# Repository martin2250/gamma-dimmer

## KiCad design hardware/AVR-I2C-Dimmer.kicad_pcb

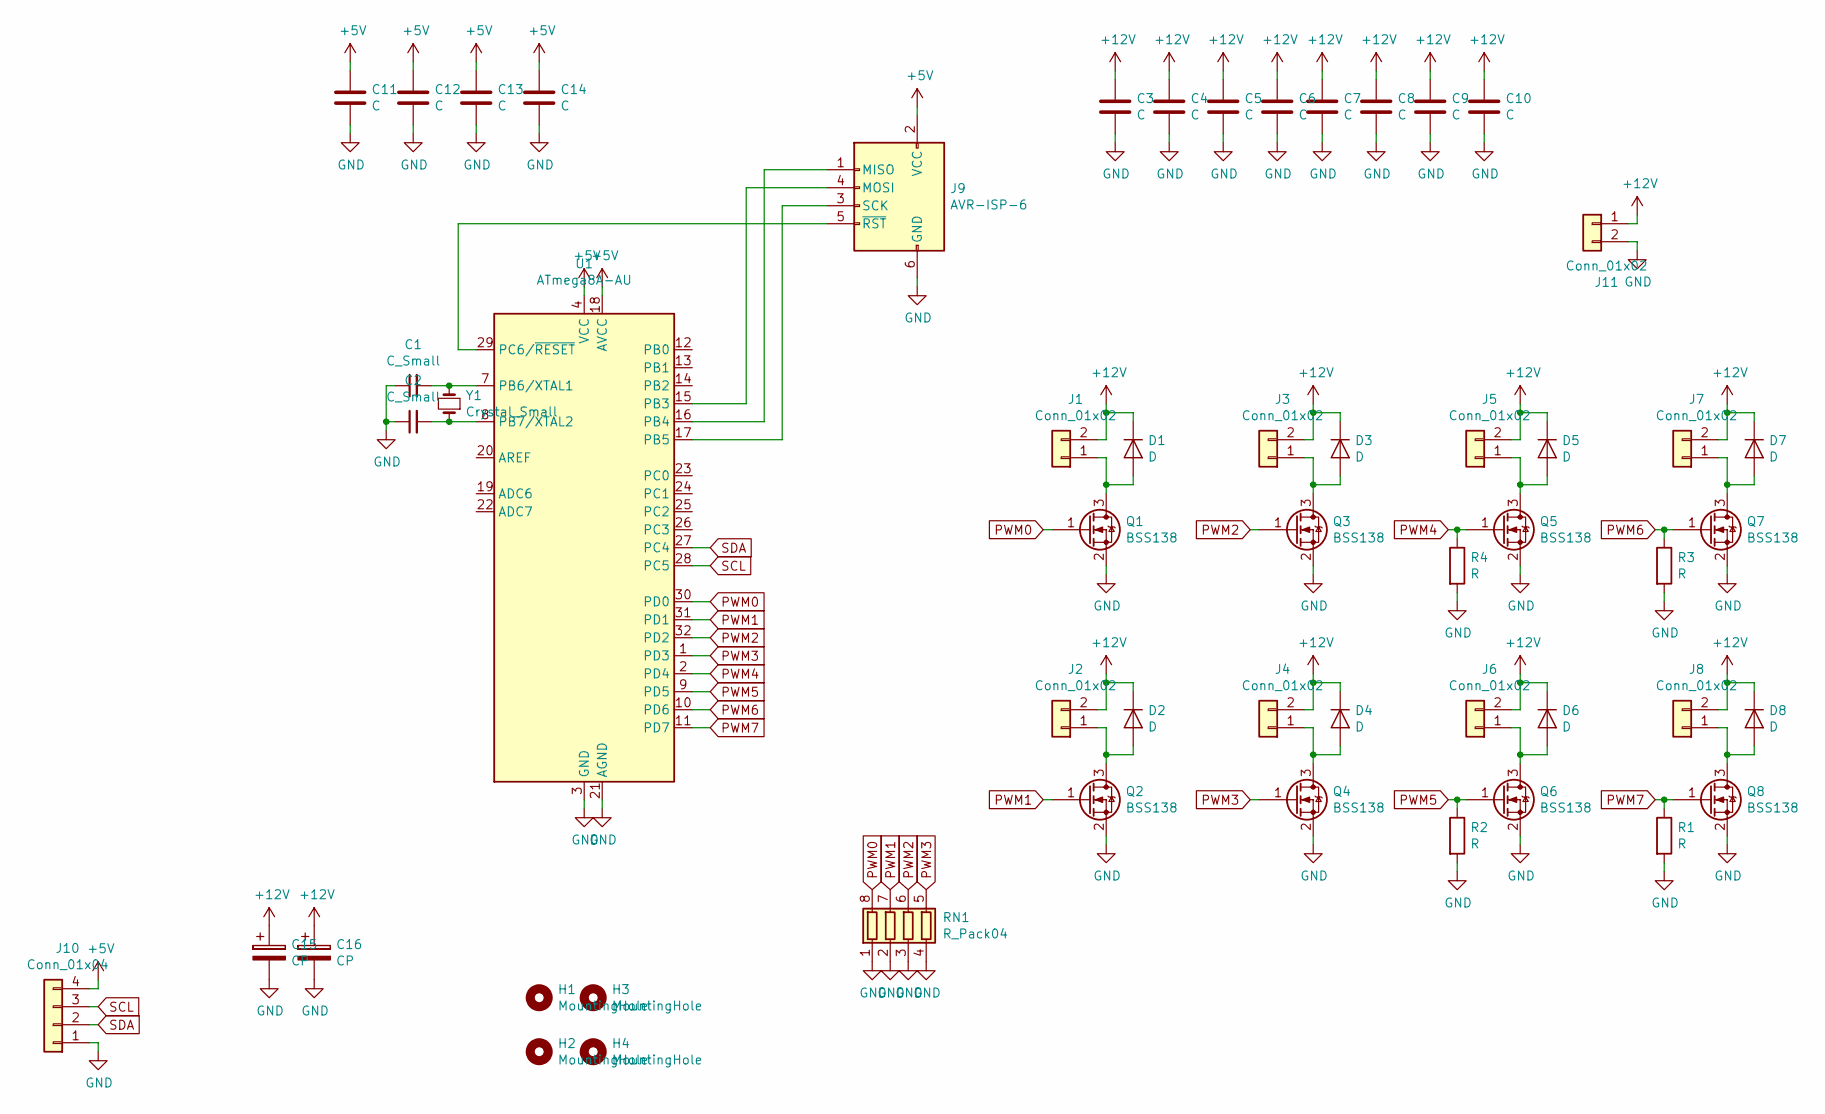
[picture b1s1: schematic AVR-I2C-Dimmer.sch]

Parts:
C1, C2: C_Small; C_0805_2012Metric_Pad1.15x1.40mm_HandSolder
C3, C4, C5, C6, C7, C8, C9, C10: C; C_1206_3216Metric_Pad1.42x1.75mm_HandSolder
C11, C12, C13, C14: C; C_0805_2012Metric_Pad1.15x1.40mm_HandSolder
C15, C16: CP; CP_Radial_D8.0mm_P3.50mm
D1, D2, D3, D4, D5, D6, D7, D8: D; D_MiniMELF
H1, H2, H3, H4: MountingHole; MountingHole_3.2mm_M3
J1, J2, J3, J4, J5, J6, J7, J8, J11: Conn_01x02; TerminalBlock_4Ucon_1x02_P3.50mm_Horizontal
J9: AVR-ISP-6; PinHeader_2x03_P2.54mm_Vertical
J10: Conn_01x04; PinHeader_1x04_P2.54mm_Vertical
Q1, Q2, Q3, Q4, Q5, Q6, Q7, Q8: BSS138; SOT-23
R1, R2, R3, R4: R; R_0805_2012Metric
RN1: R_Pack04; R_Array_Concave_4x0603
U1: ATmega8A-AU; TQFP-32_7x7mm_P0.8mm
Y1: Crystal_Small; Crystal_HC49-U_Vertical

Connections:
+5V: C11.1, C12.1, C13.1, C14.1, J9.2 (VCC), J10.4, U1.4 (VCC), U1.6 (VCC), U1.18 (AVCC)
+12V: C3.1, C4.1, C5.1, C6.1, C7.1, C8.1, C9.1, C10.1, C15.1, C16.1, D1.1 (K), D2.1 (K), D3.1 (K), D4.1 (K), D5.1 (K), D6.1 (K), D7.1 (K), D8.1 (K), J1.2, J2.2, J3.2, J4.2, J5.2, J6.2, J7.2, J8.2, J11.1
GND: C1.1, C2.1, C3.2, C4.2, C5.2, C6.2, C7.2, C8.2, C9.2, C10.2, C11.2, C12.2, C13.2, C14.2, C15.2, C16.2, J9.6 (GND), J10.1, J11.2, Q1.2 (S), Q2.2 (S), Q3.2 (S), Q4.2 (S), Q5.2 (S), Q6.2 (S), Q7.2 (S), Q8.2 (S), R1.2, R2.2, R3.2, R4.2, RN1.1 (R1.1), RN1.2 (R2.1), RN1.3 (R3.1), RN1.4 (R4.1), U1.3 (GND), U1.5 (GND), U1.21 (AGND)
unnamed: C1.2, U1.7 (PB6/XTAL1), Y1.2
unnamed: C2.2, U1.8 (PB7/XTAL2), Y1.1
unnamed: D1.2 (A), J1.1, Q1.3 (D)
unnamed: D2.2 (A), J2.1, Q2.3 (D)
unnamed: D3.2 (A), J3.1, Q3.3 (D)
unnamed: D4.2 (A), J4.1, Q4.3 (D)
unnamed: D5.2 (A), J5.1, Q5.3 (D)
unnamed: D6.2 (A), J6.1, Q6.3 (D)
unnamed: D7.2 (A), J7.1, Q7.3 (D)
unnamed: D8.2 (A), J8.1, Q8.3 (D)
unnamed: J9.1 (MISO), U1.16 (PB4)
unnamed: J9.3 (SCK), U1.17 (PB5)
unnamed: J9.4 (MOSI), U1.15 (PB3)
unnamed: J9.5 (~RST), U1.29 (PC6/~RESET)
PWM0: Q1.1 (G), RN1.8 (R1.2), U1.30 (PD0)
PWM1: Q2.1 (G), RN1.7 (R2.2), U1.31 (PD1)
PWM2: Q3.1 (G), RN1.6 (R3.2), U1.32 (PD2)
PWM3: Q4.1 (G), RN1.5 (R4.2), U1.1 (PD3)
PWM4: Q5.1 (G), R4.1, U1.2 (PD4)
PWM5: Q6.1 (G), R2.1, U1.9 (PD5)
PWM6: Q7.1 (G), R3.1, U1.10 (PD6)
PWM7: Q8.1 (G), R1.1, U1.11 (PD7)
SCL: J10.3, U1.28 (PC5)
SDA: J10.2, U1.27 (PC4)

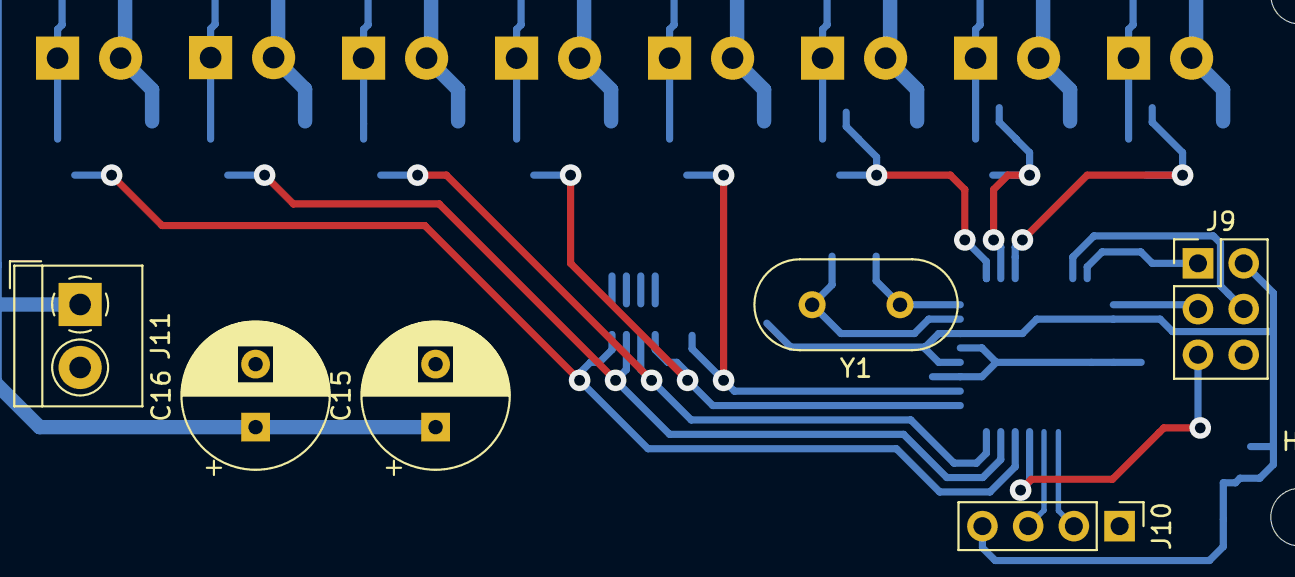
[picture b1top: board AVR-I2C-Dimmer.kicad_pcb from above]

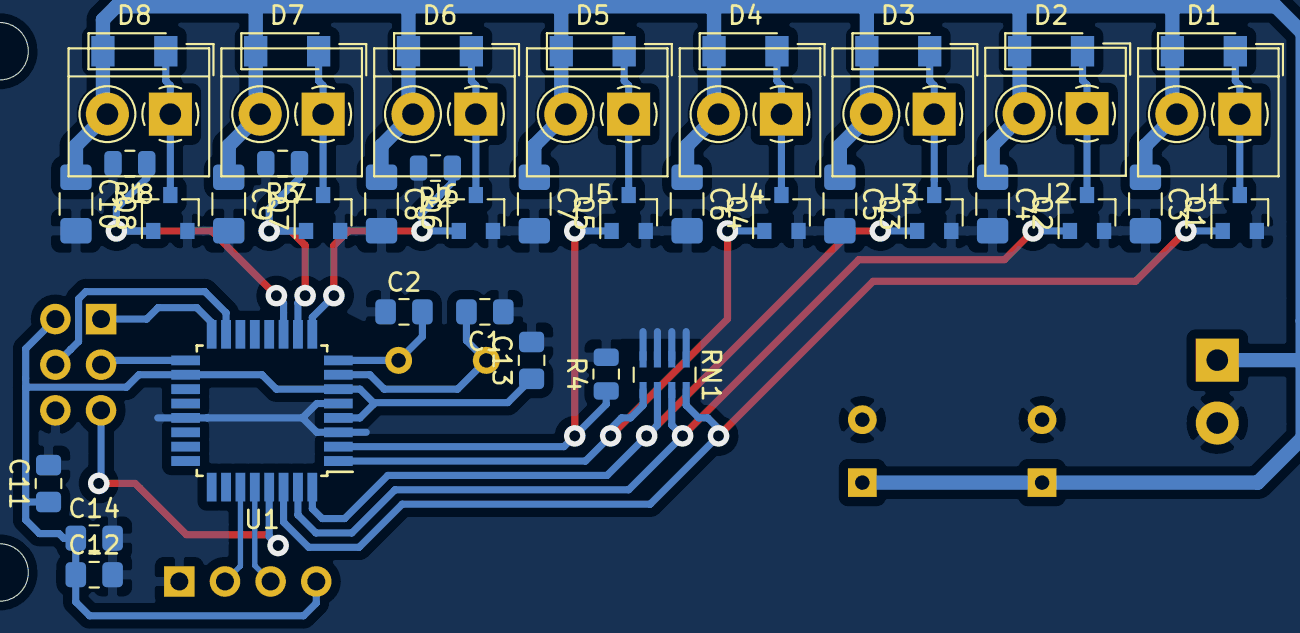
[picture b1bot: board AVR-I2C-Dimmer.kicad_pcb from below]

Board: 2 copper layers, 54 parts (44 on the bottom side), 27 nets.

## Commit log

2019-02-11 Create LICENSE
2019-02-12 expand to 256 steps
